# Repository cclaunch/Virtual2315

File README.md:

PROJECT STILL IN TESTING, WAIT TO DOWNLOAD AND USE

This project allows an IBM 1130 to protect the rare disk heads and physical 2315 disk cartridges from crashes, while still making use of the disk drive and experiencing the sounds and vibrations associated with the drive.

A file with the contents of a 2315 disk cartridge is stored on a microSD card inside a holder that looks like a miniature 2315. The project loads the content of the file into RAM when the cartridge is 'loaded', writing back the contents of RAM to the file when unloaded.

A switch and small physical modification to the drive allows it to be switched between real and virtual mode, where the drive spins a dummy cartridge and operates in conjuction with this project or the drive is left off for pure virtual mode.

Disk heads remain above the surface in either mode and our facility generates the bit stream that would come from the head during a read and grabbing new data that is sent to the drive during a write, updating the RAM contents and eventually the file.

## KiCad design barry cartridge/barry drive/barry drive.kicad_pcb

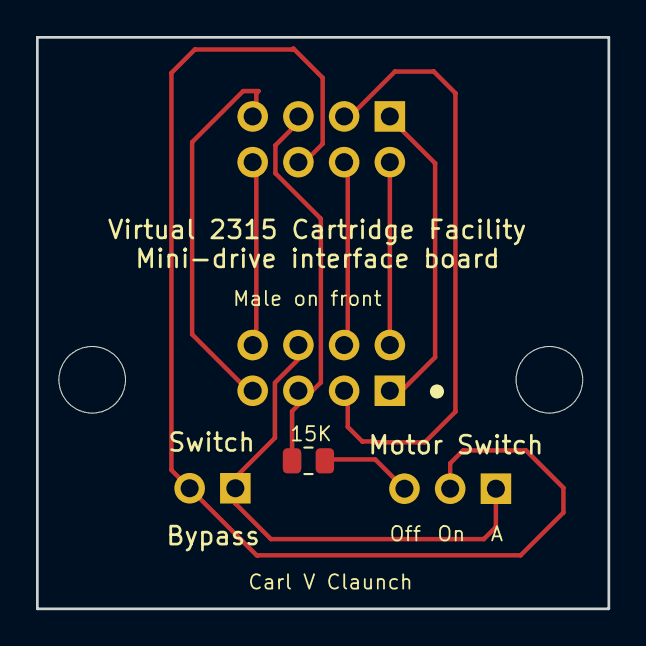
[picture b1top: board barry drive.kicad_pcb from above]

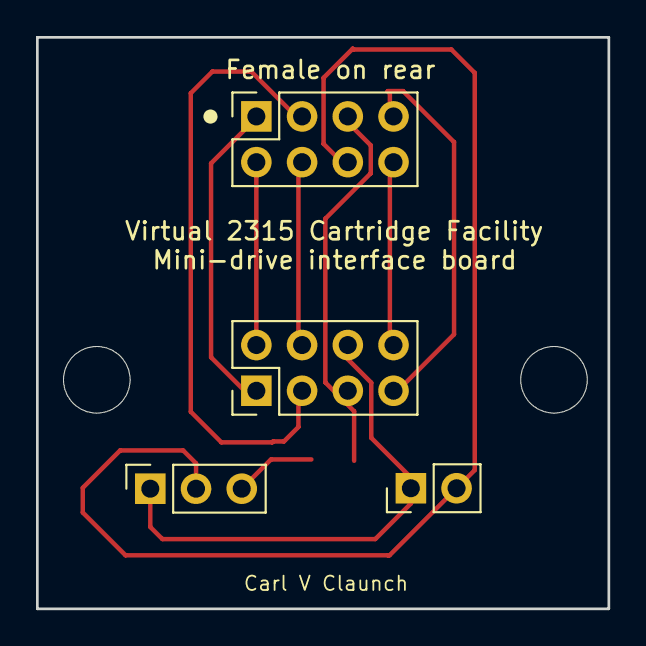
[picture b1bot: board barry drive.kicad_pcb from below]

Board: 2 copper layers, 31.7 x 31.8 mm, 7 parts (4 on the bottom side), 10 nets.

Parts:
H1, H2: MountingHole; MountingHole_3.7mm
J1: Conn_02x04_Odd_Even; PinSocket_2x04_P2.54mm_Vertical
J2: Conn_02x04_Odd_Even; PinHeader_2x04_P2.54mm_Vertical
J3: Conn_01x02_Pin; PinHeader_1x02_P2.54mm_Vertical
J4: Conn_01x03_Socket; PinSocket_1x03_P2.54mm_Vertical
R1: 15K; R_0805_2012Metric

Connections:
unnamed: J1.1, J2.1
unnamed: J1.2, J2.2
unnamed: J1.3, J2.3
unnamed: J1.4, J2.4
unnamed: J1.5, J2.5, R1.2
unnamed: J1.6, J3.2, J4.2
unnamed: J1.7, J2.7
unnamed: J1.8, J2.8
unnamed: J2.6, J3.1, J4.1
unnamed: J4.3, R1.1

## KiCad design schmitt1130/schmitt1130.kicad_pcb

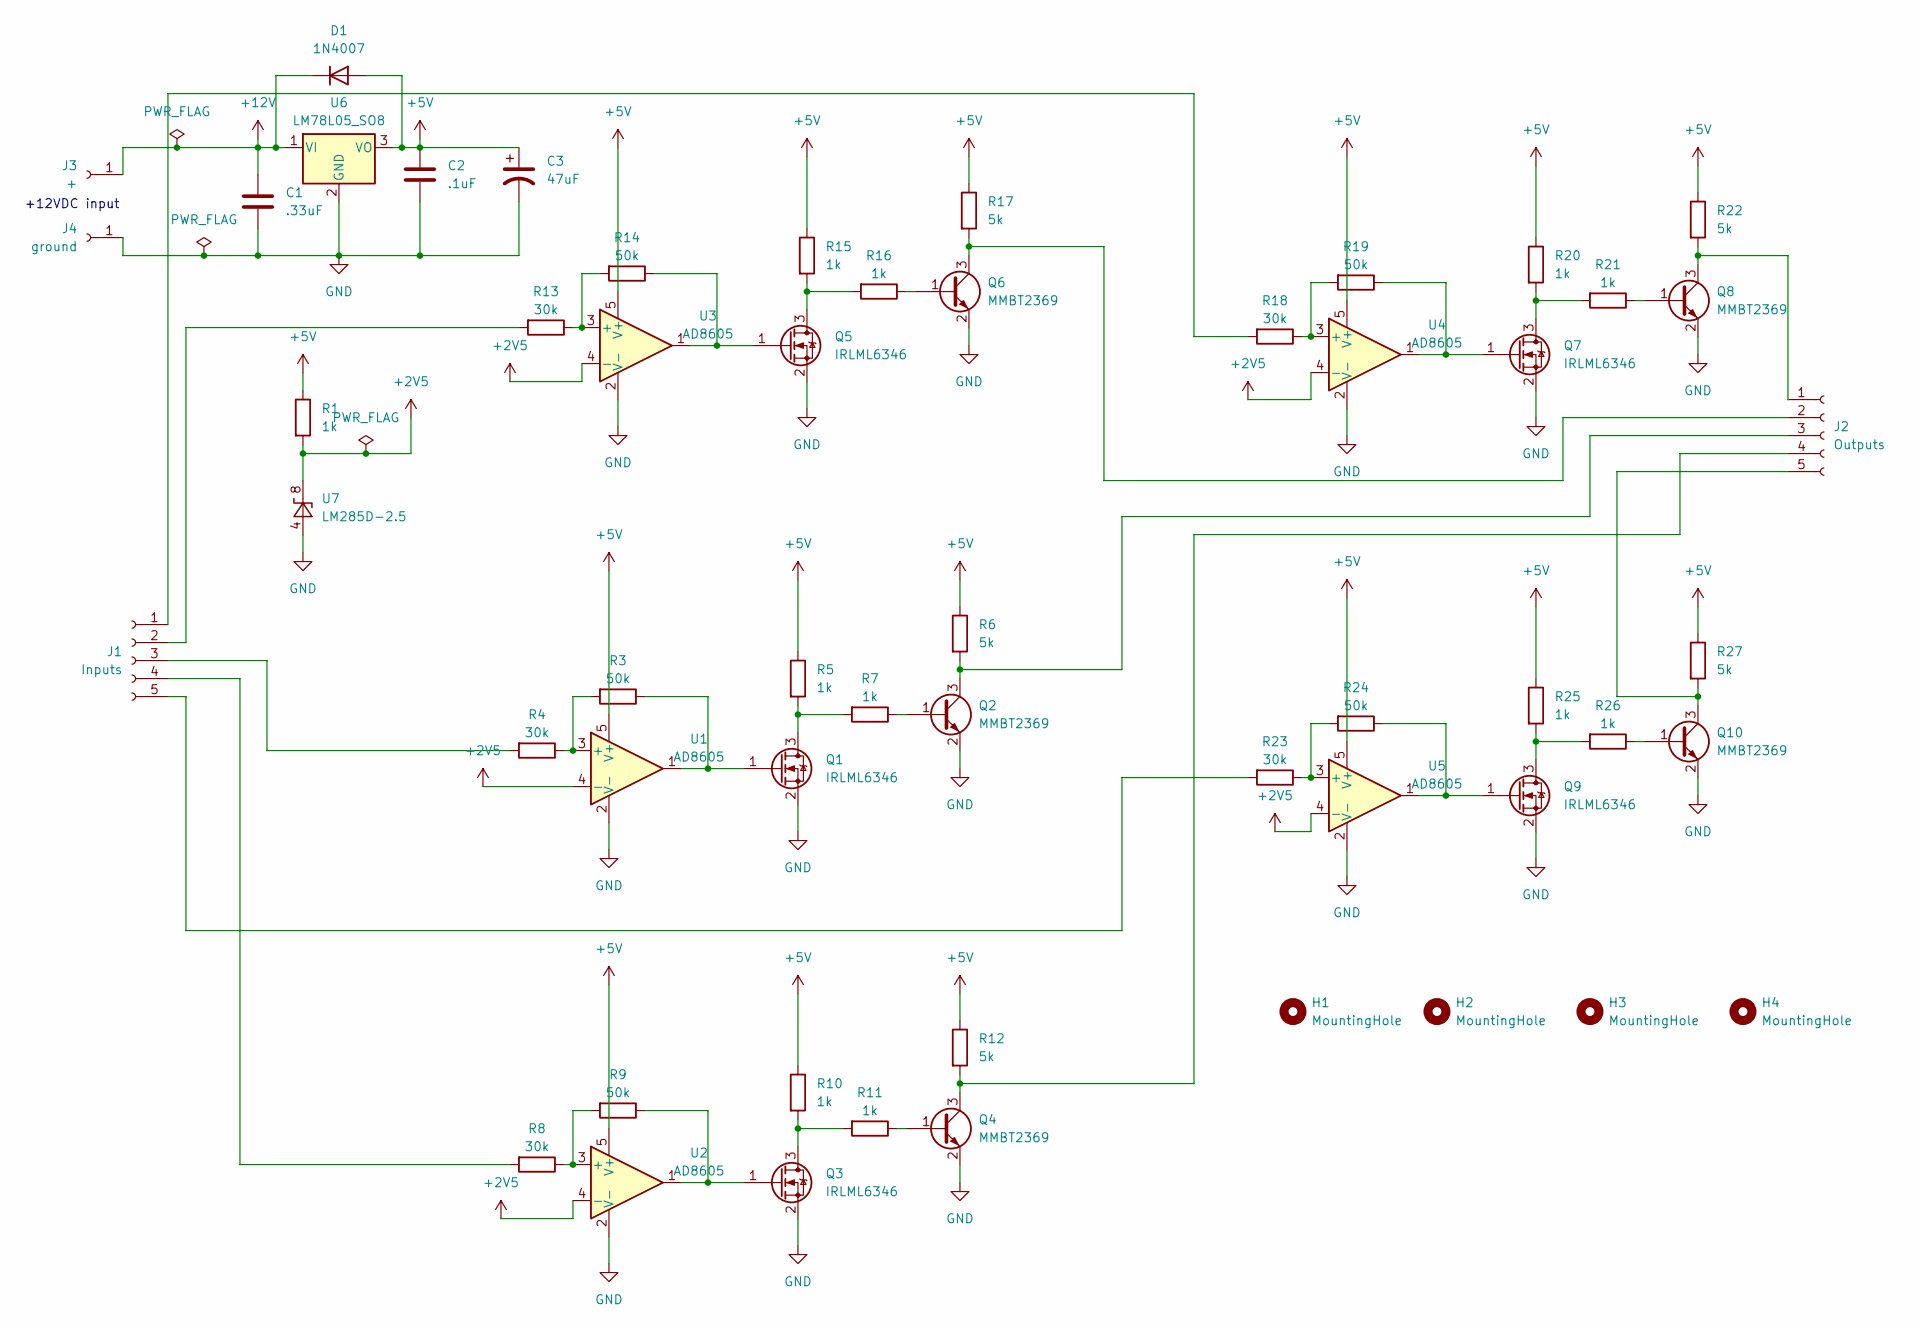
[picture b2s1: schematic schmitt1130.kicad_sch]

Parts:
C1: .33uF; C_0805_2012Metric
C2: .1uF; C_0805_2012Metric
C3: 47uF; CP_Elec_5x5.3
D1: 1N4007; D_SOD-523
H1, H2, H3, H4: MountingHole; MountingHole_4.3mm_M4
J1: Inputs; PinSocket_1x05_P2.54mm_Vertical
J2: Outputs; PinSocket_1x05_P2.54mm_Vertical
J3: +; SolderWire-0.75sqmm_1x01_D1.25mm_OD3.5mm
J4: ground; SolderWire-0.75sqmm_1x01_D1.25mm_OD3.5mm
Q1, Q3, Q5, Q7, Q9: IRLML6346; SOT-23
Q2, Q4, Q6, Q8, Q10: MMBT2369; SOT-23
R1, R5, R7, R10, R11, R15, R16, R20, R21, R25, R26: 1k; R_0805_2012Metric
R3, R9, R14, R19, R24: 50k; R_0805_2012Metric
R4, R8, R13, R18, R23: 30k; R_0805_2012Metric
R6, R12, R17, R22, R27: 5k; R_0805_2012Metric
U1, U2, U3, U4, U5: AD8605; TSOT-23-5
U6: LM78L05_SO8; SOT-223-3_TabPin2
U7: LM285D-2.5; SOIC-8_3.9x4.9mm_P1.27mm

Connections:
+2V5: R1.2, U1.4 (-), U2.4 (-), U3.4 (-), U4.4 (-), U5.4 (-), U7.8 (K)
+5V: C2.1, C3.1, D1.2 (A), R1.1, R5.1, R6.1, R10.1, R12.1, R15.1, R17.1, R20.1, R22.1, R25.1, R27.1, U1.5 (V+), U2.5 (V+), U3.5 (V+), U4.5 (V+), U5.5 (V+), U6.3 (VO)
+12V: C1.1, D1.1 (K), J3.1, U6.1 (VI)
GND: C1.2, C2.2, C3.2, J4.1, Q1.2 (S), Q2.2 (E), Q3.2 (S), Q4.2 (E), Q5.2 (S), Q6.2 (E), Q7.2 (S), Q8.2 (E), Q9.2 (S), Q10.2 (E), U1.2 (V-), U2.2 (V-), U3.2 (V-), U4.2 (V-), U5.2 (V-), U6.2 (GND), U7.4 (A)
unnamed: J1.1, R18.2
unnamed: J1.2, R13.2
unnamed: J1.3, R4.2
unnamed: J1.4, R8.2
unnamed: J1.5, R23.2
unnamed: J2.1, Q8.3 (C), R22.2
unnamed: J2.2, Q6.3 (C), R17.2
unnamed: J2.3, Q2.3 (C), R6.2
unnamed: J2.4, Q4.3 (C), R12.2
unnamed: J2.5, Q10.3 (C), R27.2
unnamed: Q1.3 (D), R5.2, R7.2
unnamed: Q1.1 (G), R3.1, U1.1
unnamed: Q2.1 (B), R7.1
unnamed: Q3.3 (D), R10.2, R11.2
unnamed: Q3.1 (G), R9.1, U2.1
unnamed: Q4.1 (B), R11.1
unnamed: Q5.3 (D), R15.2, R16.2
unnamed: Q5.1 (G), R14.1, U3.1
unnamed: Q6.1 (B), R16.1
unnamed: Q7.3 (D), R20.2, R21.2
unnamed: Q7.1 (G), R19.1, U4.1
unnamed: Q8.1 (B), R21.1
unnamed: Q9.3 (D), R25.2, R26.2
unnamed: Q9.1 (G), R24.1, U5.1
unnamed: Q10.1 (B), R26.1
unnamed: R3.2, R4.1, U1.3 (+)
unnamed: R8.1, R9.2, U2.3 (+)
unnamed: R13.1, R14.2, U3.3 (+)
unnamed: R18.1, R19.2, U4.3 (+)
unnamed: R23.1, R24.2, U5.3 (+)

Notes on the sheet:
+12VDC input

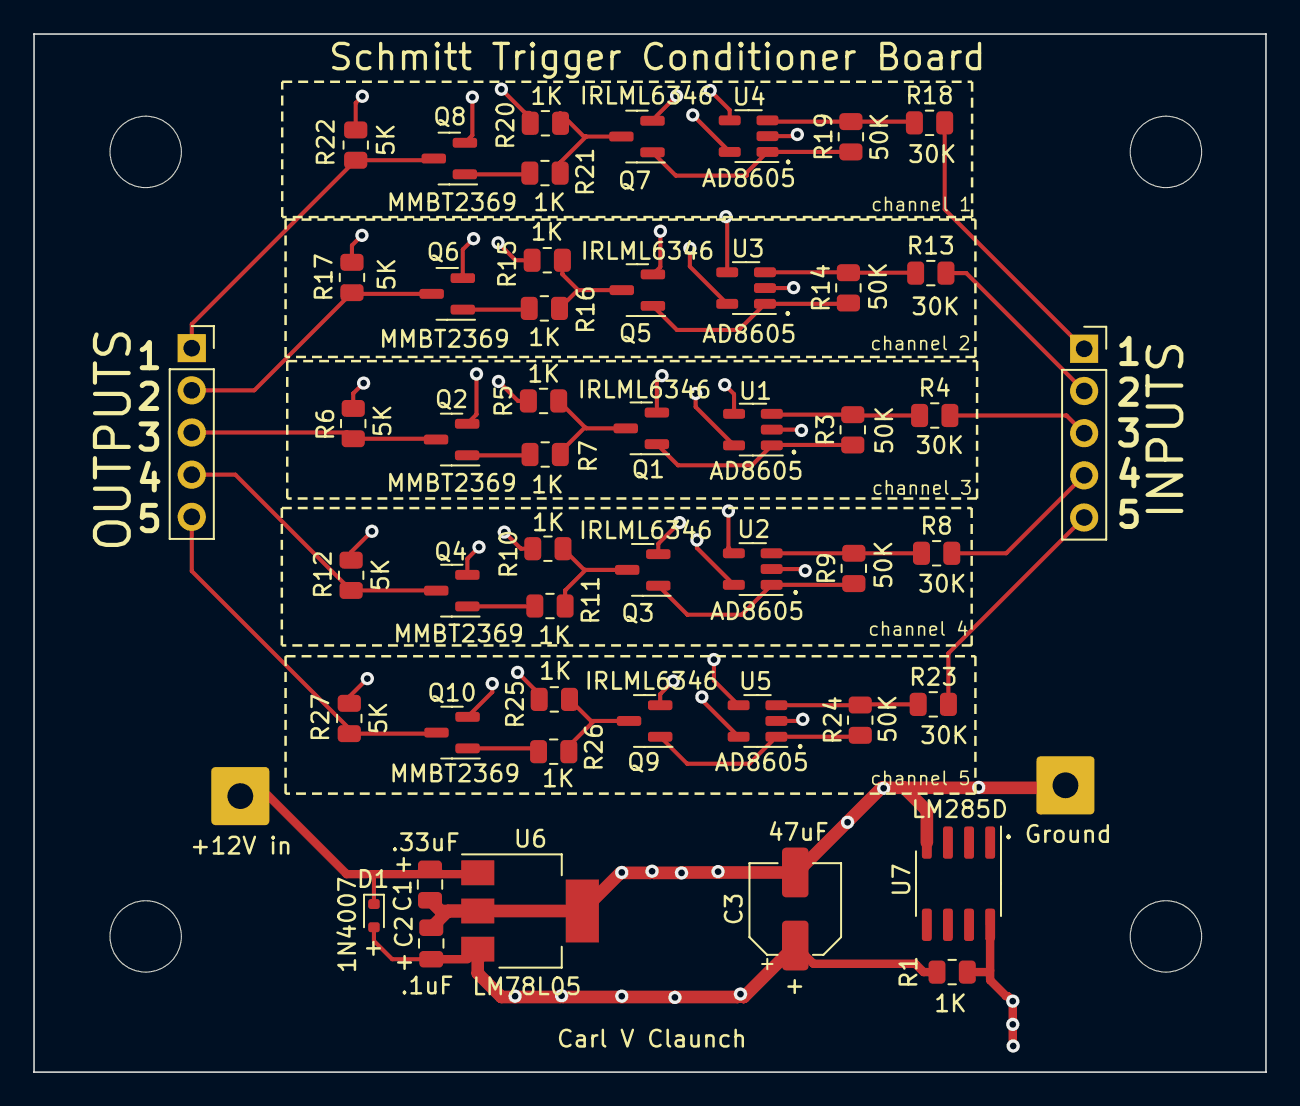
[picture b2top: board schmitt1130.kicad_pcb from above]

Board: 4 copper layers, 74.2 x 62.5 mm, 55 parts (0 on the bottom side), 34 nets.

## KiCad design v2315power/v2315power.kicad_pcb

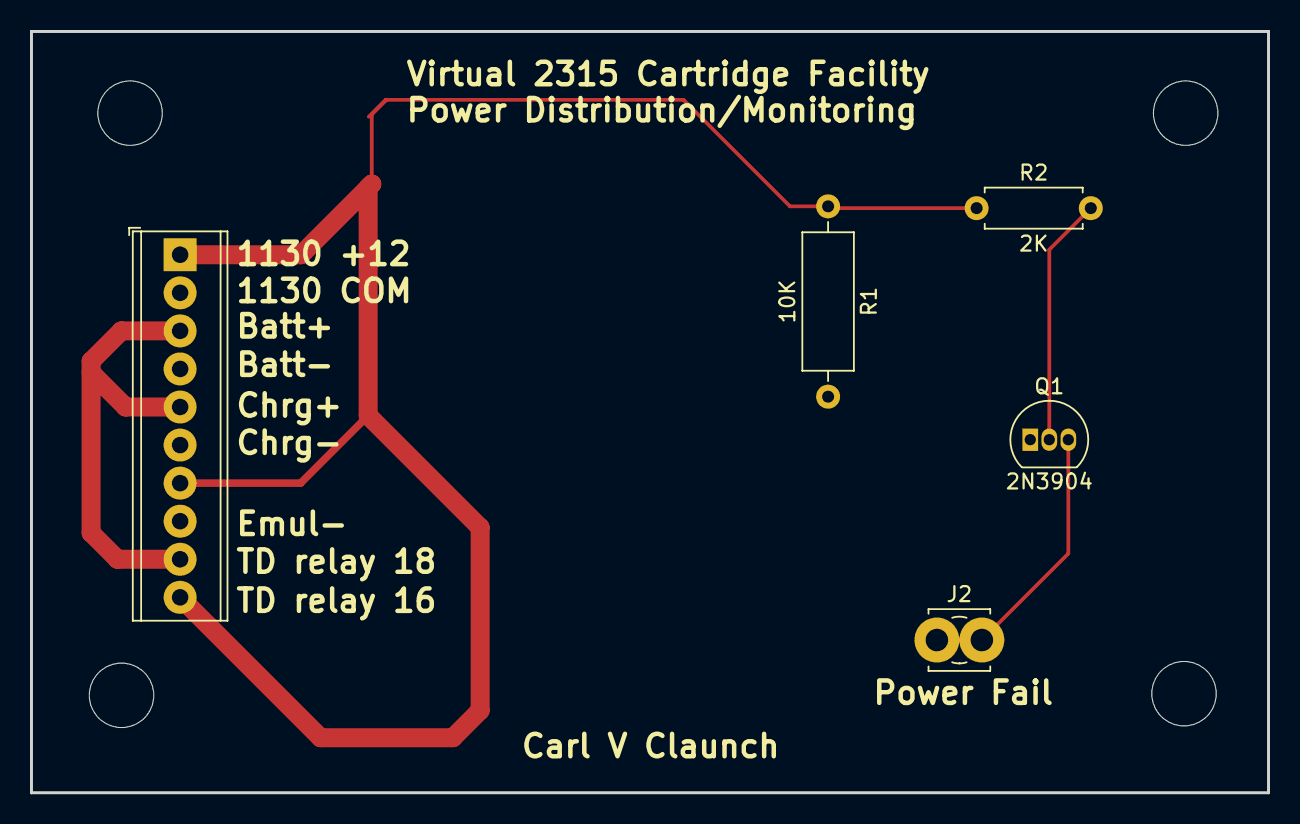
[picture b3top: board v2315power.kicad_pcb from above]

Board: 2 copper layers, 82.5 x 50.8 mm, 9 parts (0 on the bottom side), 5 nets.

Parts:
H1, H2, H3, H4: MountingHole; MountingHole_4.3mm_M4
J1: Screw_Terminal_01x10; TerminalBlock_Phoenix_MPT-0,5-10-2.54_1x10_P2.54mm_Horizont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
J2: Screw_Terminal_01x01; TerminalBlock_MetzConnect_360272_1x01_Horizontal_ScrewM2.6
Q1: 2N3904; TO-92_Inline
R1: 10K; R_Axial_DIN0309_L9.0mm_D3.2mm_P12.70mm_Horizontal
R2: 2K; R_Axial_DIN0207_L6.3mm_D2.5mm_P7.62mm_Horizontal

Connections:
GNDREF: J1.2, J1.4, J1.6, J1.8, Q1.1 (E), R1.2
unnamed: J1.3, J1.5, J1.9
unnamed: J1.1, J1.7, J1.10, R1.1, R2.1
unnamed: J2.1, Q1.3 (C)
unnamed: Q1.2 (B), R2.2

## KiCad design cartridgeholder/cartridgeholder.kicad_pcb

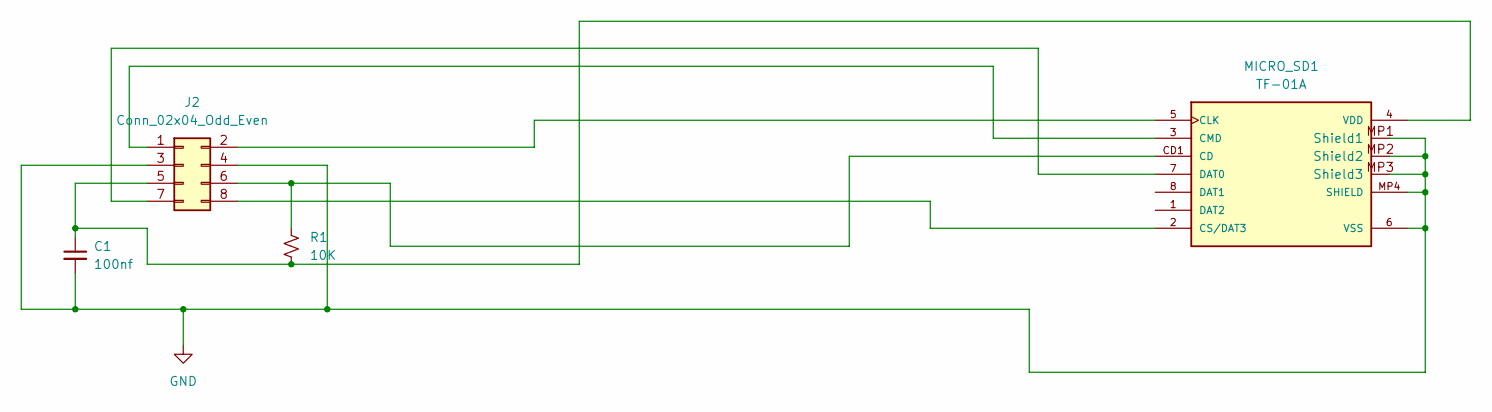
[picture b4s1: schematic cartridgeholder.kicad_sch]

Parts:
C1: 100nf
J2: Conn_02x04_Odd_Even
MICRO_SD1: TF-01A
R1: 10K

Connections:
GND: C1.2, J2.3, J2.4, MICRO_SD1.6 (VSS), MICRO_SD1.MP1 (Shield1), MICRO_SD1.MP2 (Shield2), MICRO_SD1.MP3 (Shield3), MICRO_SD1.MP4 (SHIELD)
unnamed: J2.1, MICRO_SD1.3 (CMD)
unnamed: J2.2, MICRO_SD1.5 (CLK)
unnamed: C1.1, J2.5, MICRO_SD1.4 (VDD), R1.2
unnamed: J2.6, MICRO_SD1.CD1 (CD), R1.1
unnamed: J2.7, MICRO_SD1.7 (DAT0)
unnamed: J2.8, MICRO_SD1.2 (CS/DAT3)

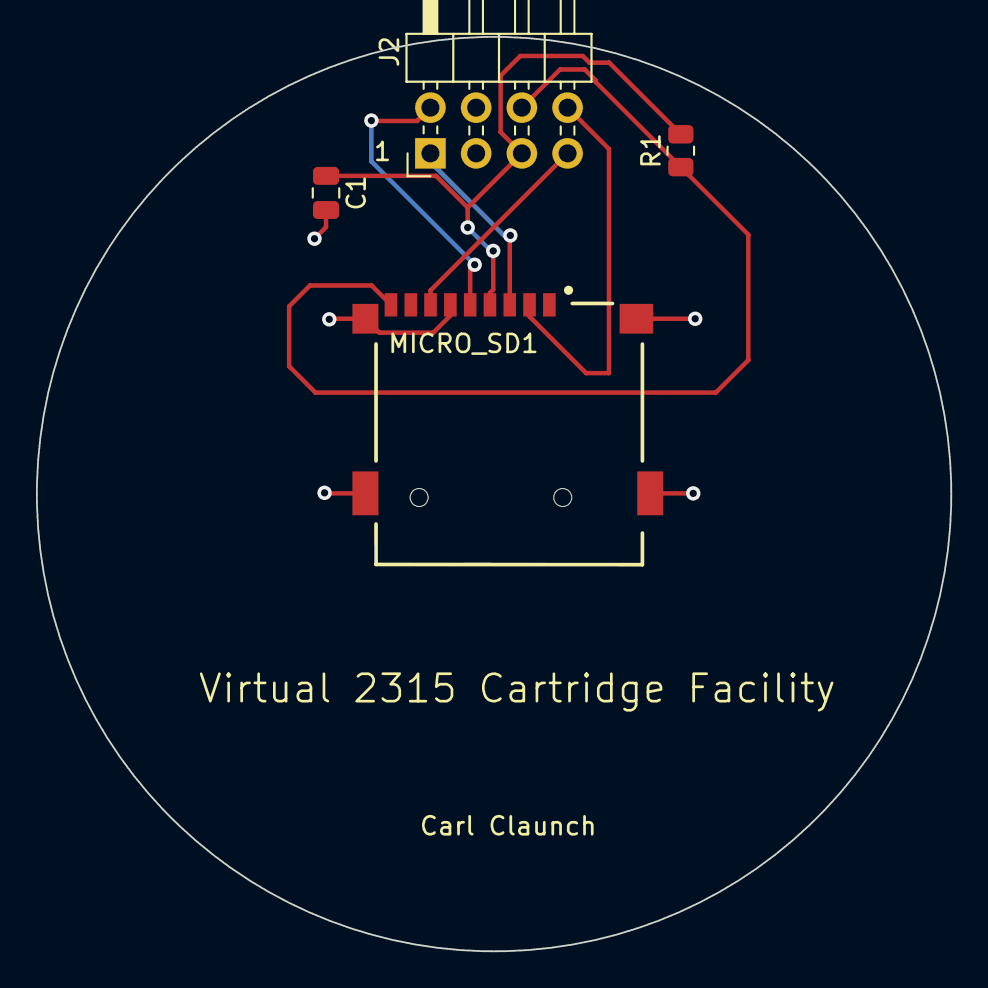
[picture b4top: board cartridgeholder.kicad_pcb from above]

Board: 2 copper layers, 50.8 x 50.8 mm, 4 parts (0 on the bottom side), 7 nets.

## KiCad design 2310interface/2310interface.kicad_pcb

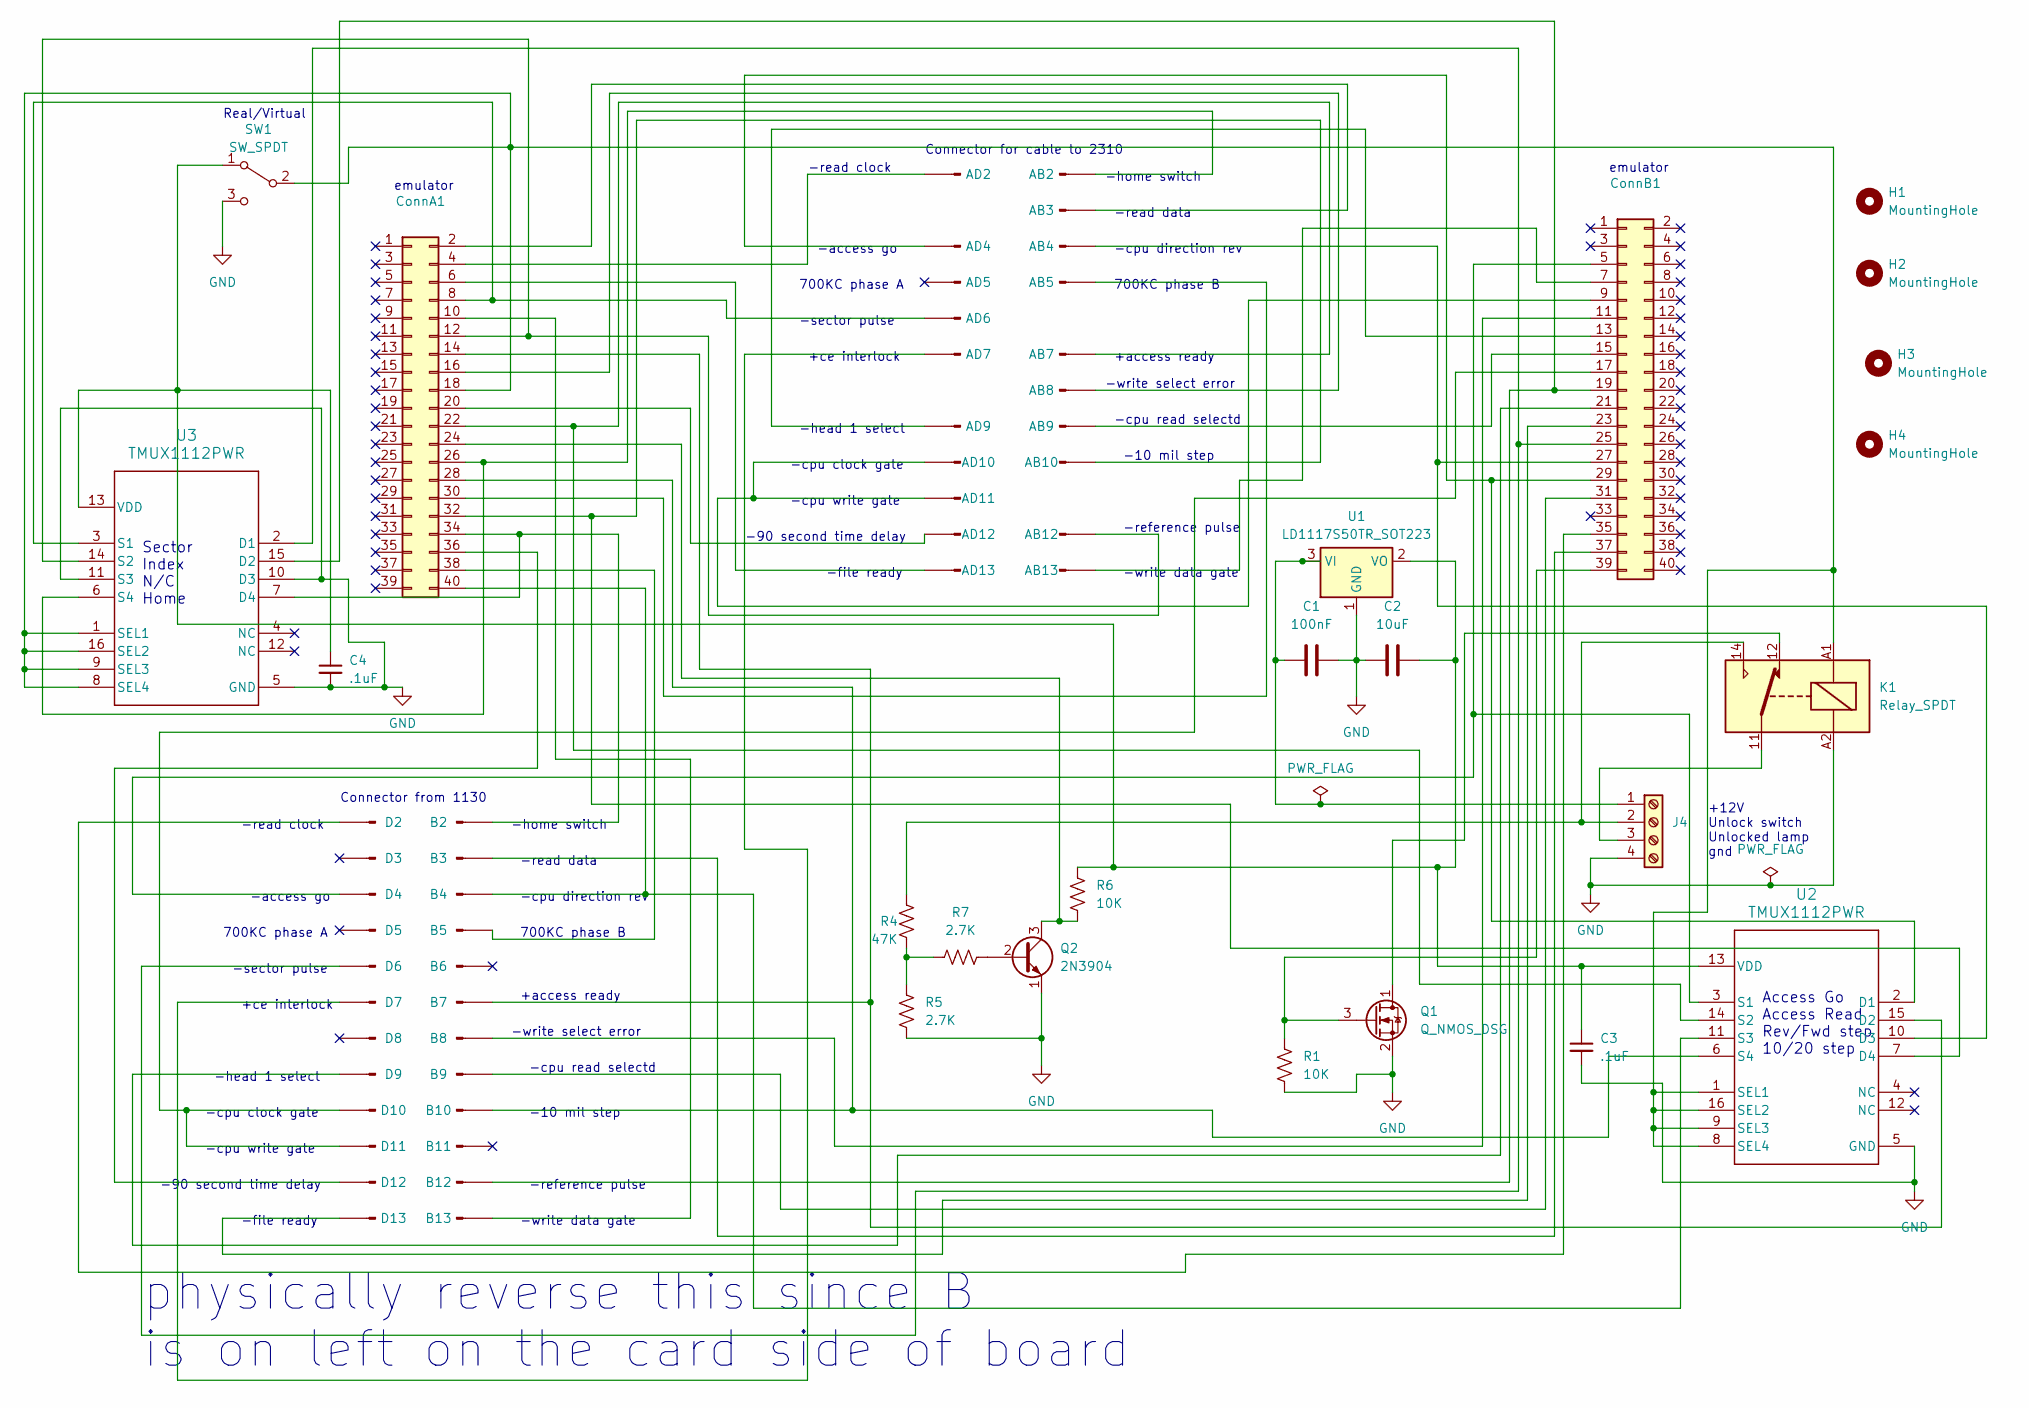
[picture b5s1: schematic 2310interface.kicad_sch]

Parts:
AB2, AB3, AB4, AB5, AB7, AB8, AB9, AB10, AB12, AB13: Conn_01x01_Pin; SolderWire-1sqmm_1x01_D1.4mm_OD3.9mm
AD2, AD4, AD5, AD6, AD7, AD9, AD10, AD11, AD12, AD13: Conn_01x01_Pin; SolderWire-1sqmm_1x01_D1.4mm_OD3.9mm
B2, B3, B4, B5, B6, B7, B8, B9, B10, B11, B12, B13: Conn_01x01_Pin; SLT
C1: 100nF; C_0805_2012Metric
C2: 10uF; C_0805_2012Metric
C3, C4: .1uF; C_0805_2012Metric
ConnA1: Conn_02x20_Odd_Even; IDC-Header_2x20_P2.54mm_Latch_Horizontal
ConnB1: Conn_02x20_Odd_Even; IDC-Header_2x20_P2.54mm_Latch_Horizontal
D2, D3, D4, D5, D6, D7, D8, D9, D10, D11, D12, D13: Conn_01x01_Pin; SLT
H1, H2, H3, H4: MountingHole; MountingHole_4mm
J4: Screw_Terminal_01x04; TerminalBlock_Phoenix_MKDS-1,5-4_1x04_P5.00mm_Horizontal
K1: Relay_SPDT; Relay_SPDT_Finder_36.11
Q1: Q_NMOS_DSG; TO-220AB
Q2: 2N3904; TO-92_Inline
R1, R6: 10K; R_0805_2012Metric
R4: 47K; R_0805_2012Metric
R5, R7: 2.7K; R_0805_2012Metric
SW1: SW_SPDT; SW_SPDT_PCM12
U1: LD1117S50TR_SOT223; SOT-223-3_TabPin2
U2, U3: TMUX1112PWR; PW0016A-MFG

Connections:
GND: C1.1, C2.2, C3.2, C4.2, J4.4, K1.A2, Q1.2 (S), Q2.1 (E), R1.2, R5.2, SW1.3 (C), U1.1 (GND), U2.5 (GND), U3.5 (GND), U3.10 (D3), U3.11 (S3)
unnamed: AB2.1, ConnA1.26, U3.6 (S4)
unnamed: AB3.1, ConnA1.2
unnamed: AB4.1, ConnB1.27, U2.10 (D3)
unnamed: AB5.1, ConnA1.30
unnamed: AB7.1, ConnA1.22, U2.14 (S2)
unnamed: AB8.1, ConnA1.16
unnamed: AB9.1, ConnB1.15
unnamed: AB10.1, ConnA1.32, U2.7 (D4)
unnamed: AB12.1, ConnA1.12, U3.14 (S2)
unnamed: AB13.1, ConnB1.7
unnamed: AD2.1, ConnA1.4
unnamed: AD4.1, ConnB1.29, U2.2 (D1)
unnamed: AD6.1, ConnA1.8, U3.3 (S1)
unnamed: AD7.1, D7.1
unnamed: AD9.1, ConnB1.13
unnamed: AD10.1, AD11.1, ConnB1.9
unnamed: AD12.1, ConnA1.20
unnamed: AD13.1, ConnA1.6
unnamed: B2.1, ConnA1.34, U3.7 (D4)
unnamed: B3.1, ConnB1.37
unnamed: B4.1, ConnA1.40, U2.11 (S3)
unnamed: B5.1, ConnA1.38
unnamed: B7.1, ConnA1.14, U2.15 (D2)
unnamed: B8.1, ConnB1.11
unnamed: B9.1, ConnB1.31
unnamed: B10.1, ConnA1.28, U2.6 (S4)
unnamed: B12.1, ConnB1.19, U3.15 (D2)
unnamed: B13.1, ConnA1.10
unnamed: ConnA1.18, K1.A1, SW1.2 (B), U2.1 (SEL1), U2.8 (SEL4), U2.9 (SEL3), U2.16 (SEL2), U3.1 (SEL1), U3.8 (SEL4), U3.9 (SEL3), U3.16 (SEL2)
unnamed: ConnA1.24, Q2.3 (C), R6.2
unnamed: ConnA1.36, D12.1
unnamed: ConnB1.5, D4.1, U2.3 (S1)
unnamed: ConnB1.17, D10.1, D11.1
unnamed: ConnB1.21, D9.1
unnamed: ConnB1.23, D13.1
unnamed: ConnB1.25, D6.1, U3.2 (D1)
unnamed: ConnB1.35, D2.1
unnamed: ConnB1.39, Q1.3 (G), R1.1
unnamed: C1.2, J4.1, U1.3 (VI)
unnamed: J4.2, K1.14, R4.1
unnamed: J4.3, K1.11
unnamed: K1.12, Q1.1 (D)
unnamed: Q2.2 (B), R7.1
unnamed: R4.2, R5.1, R7.2
unnamed: C2.1, C3.1, C4.1, R6.1, SW1.1 (A), U1.2 (VO), U2.13 (VDD), U3.13 (VDD)

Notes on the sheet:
-file ready
700KC phase A
-reference pulse
+access ready
-access go
-cpu direction rev
-sector pulse
-90 second time delay
-read clock
Sector Index N/C Home
-read data
Connector from 1130
-home switch
+ce interlock
-10 mil step
-cpu clock gate
-write select error
emulator
-write data gate
Connector for cable to 2310
-cpu read selectd
700KC phase B
-head 1 select
Access Go Access Read Rev/Fwd step 10/20 step
physically reverse this since B is on left on the card side of board
+12V Unlock switch Unlocked lamp gnd
Real/Virtual
-cpu write gate

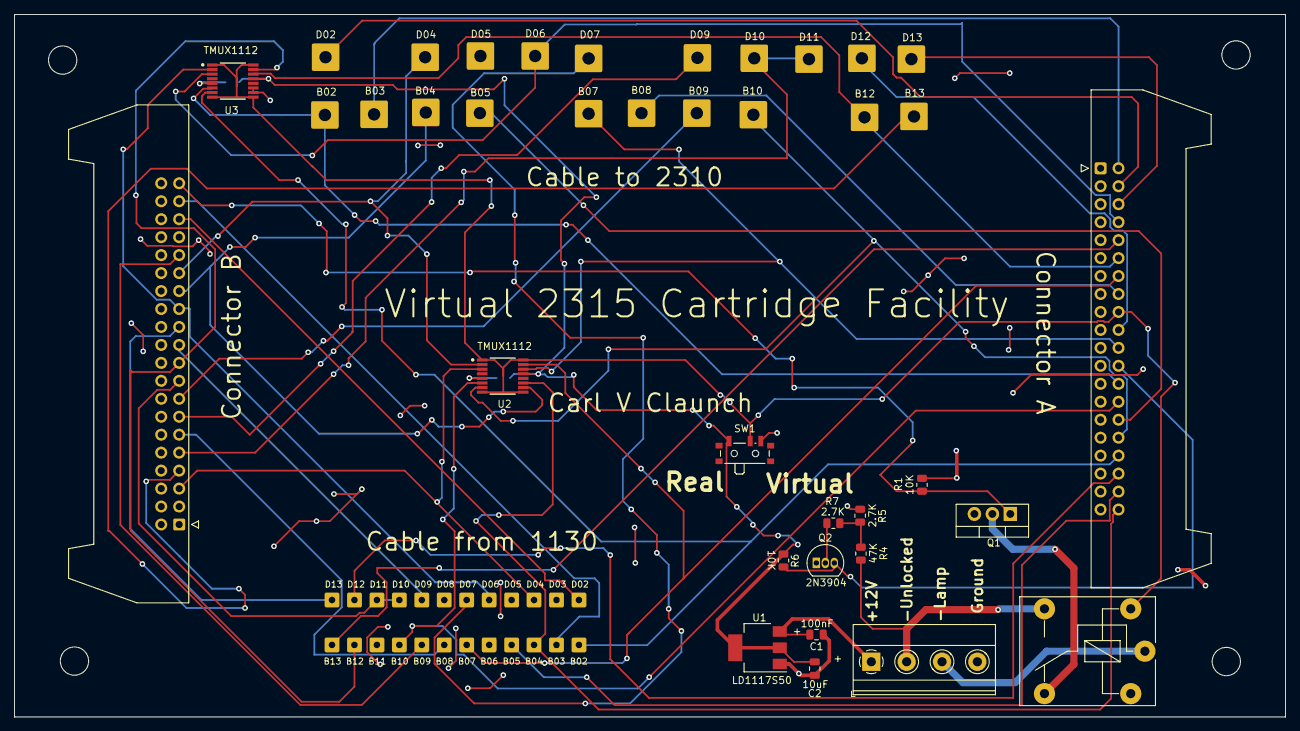
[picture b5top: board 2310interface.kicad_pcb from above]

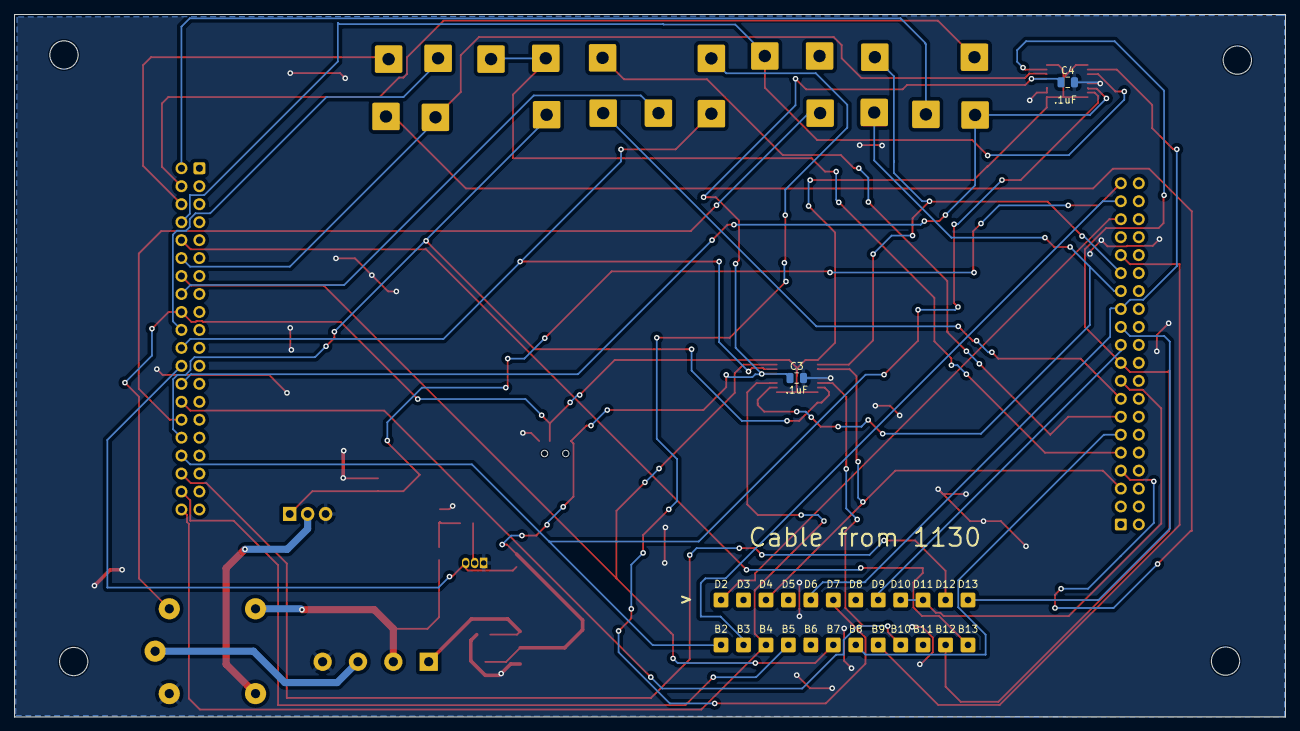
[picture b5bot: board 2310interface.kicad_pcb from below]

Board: 2 copper layers, 179.8 x 99.3 mm, 67 parts (26 on the bottom side), 46 nets.

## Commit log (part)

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2024-03-12 Initial setup
2025-03-17 Update README.md
    Better overview of the project
2025-03-17 Provide block diagram
    This shows the various units involved in the Virtual 2315 Cartridge Facility.
    Pictures are of prototype versions of some boards; real hardware is somewhat changed.
    The connections shown are symbolic.
2025-03-22 Initial upload
2025-03-22 Initial upload
    Utility programs written in Python for use with the V2315CF
2025-03-22 Initial upload
    Verilog for the FPGA portion of the V2315CF
2025-03-22 Initial upload
    Pico programs for the V2315CF
2025-03-22 Initial upload
    Showing changes to signals from RK-05 Emulator to V2315CF
2025-03-22 Create Location of RK-05 Emulator files
2025-03-22 Create Modifying RK-05 Build Instructions
    Changes to build of the RK-05 Emulator
2025-03-22 Create RK-05 Emulator kits to buy
2025-03-22 Update Modifying RK-05 Build Instructions
    added terminator modification
2025-03-22 Add files via upload
    New dress faceplate for V2315CF instead of RK05 Emulator
2025-03-22 Add files via upload
    2310 Interface Board to connect signals between disk drive and 1130
2025-03-22 Add files via upload
    PCB to make Mini 2315 Cartridge objects
2025-03-22 Add files via upload
    PCB for Power Distribution Board
2025-03-22 Add files via upload
    Bitmap to load into FPGA via Lattice Programmer onto board JTAG connector
2025-03-22 Add files via upload
    Pico executable, drag and drop into Pico window to load firmware
2025-03-22 Create Parts for power system
    pointer to my choices for 12V battery, charger and timer module
2025-03-22 Add files via upload
    File to 3D print plastic bottom cover for Mini 2315 Cartridge object
2025-03-22 Update Modifying RK-05 Build Instructions
    more specificity on where to add resistor and possible donor site.
2025-03-23 New version
    tag the converted disk file with the date and time of creation
2025-03-23 New version
    Displays date and time of file conversion for each detected file
2025-04-10 Update after testing
2025-04-10 Removing unnecessary files
2025-04-10 Remove unnecessary files
2025-04-10 Testing warning
2025-04-10 Fix defect in board
    Inadvertent connection of +12V to the Unlock lamp driver
    also increased current capacity for Unlock lamp traces
2025-04-11 Edited manual
    Added detail, cleaned up writing
2025-04-11 Minor change
    Changed strobe_selected_ready to length of Access_Drive signal not single pulse, to restore logging of commands in the PICO
